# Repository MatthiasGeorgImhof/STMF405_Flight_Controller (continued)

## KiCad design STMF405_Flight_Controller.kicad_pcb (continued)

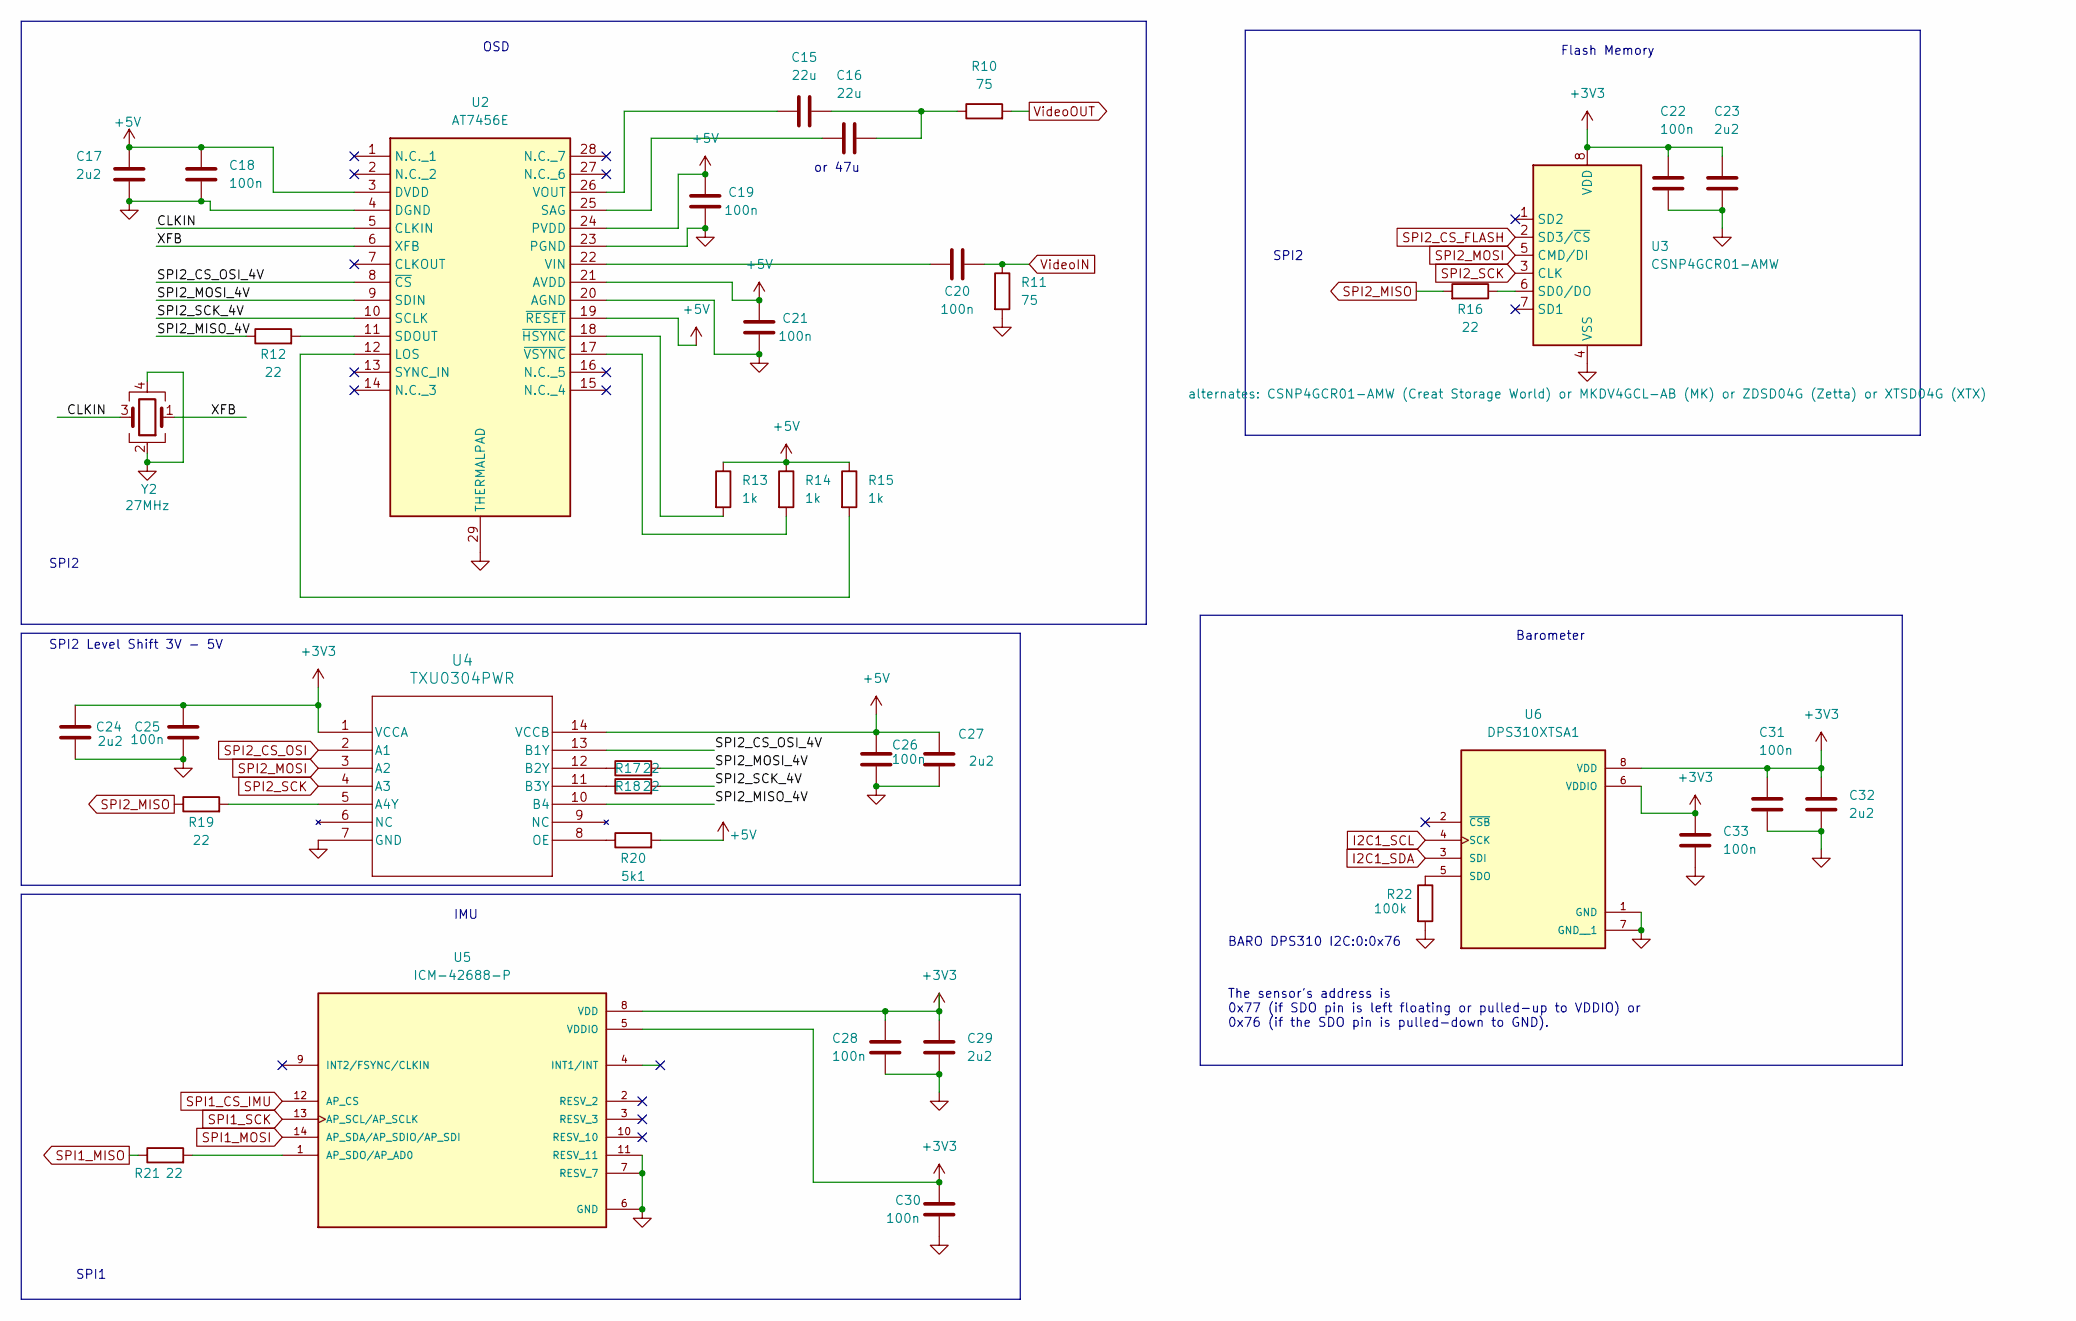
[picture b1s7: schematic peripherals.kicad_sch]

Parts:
C15, C16: 22u; C_0805_2012Metric; Voltage 25; Tolerance 20%; Part Number GRM21BR61E226ME44K
C17, C23, C24, C27, C29, C32: 2u2; C_0402_1005Metric; Voltage 25; Tolerance 10%; Part Number GRT155R61E225KE13D
C18, C19, C20, C21, C22, C25, C26, C28, C30, C31, C33: 100n; C_0201_0603Metric; Voltage 25; Tolerance 10%; Part Number GRM033R61E104KE14J
R10, R11: 75; R_0201_0603Metric; Tolerance 1%; Part Number RC0201FR-0775RL
R12, R16, R17, R18, R19, R21: 22; R_0201_0603Metric; Tolerance 1%; Part Number RC0201FR-0722RL
R13, R14, R15: 1k; R_0201_0603Metric; Tolerance 1%; Part Number RC0201FR-071KL
R20: 5k1; R_0201_0603Metric; Tolerance 1%; Part Number RC0201FR-075K1L
R22: 100k; R_0201_0603Metric; Tolerance 1%; Part Number RC0201FR-07100KL
U2: AT7456E; SOP65P640X120-29N; Part Number AT7456E
U3: CSNP4GCR01-AMW; LGA-8_8x6mm_P1.27mm; Part Number CSNP4GCR01-AMW
U4: TXU0304PWR; TSSOP14_PW_TEX; Part Number TXU0304PWR
U5: ICM-42688-P; LGA-14_3x2.5mm_P0.5mm_LayoutBorder3x4y_no_mask_bridges; Part Number ICM-42688-P
U6: DPS310XTSA1; XDCR_DPS310XTSA1; Part Number DPS310XTSA1
Y2: 27MHz; XTAL_ECS-270-20-30B-TR; Part Number ECS-270-18-30B-JEM-TR

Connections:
+3V3: C22.1, C23.1, C24.1, C25.2, C28.1, C29.1, C30.1, C31.1, C32.1, C33.1, U3.8 (VDD), U4.1 (VCCA), U5.5 (VDDIO), U5.8 (VDD), U6.6 (VDDIO), U6.8 (VDD); also elsewhere on the board
+5V: C17.1, C18.1, C19.2, C21.2, C26.2, C27.1, R13.1, R14.1, R15.1, R20.2, U2.3 (DVDD), U2.19 (~RESET), U2.21 (AVDD), U2.24 (PVDD), U4.14 (VCCB); also elsewhere on the board
/Peripherals/CLKIN: U2.5 (CLKIN), Y2.3
/Peripherals/SPI2_CS_OSI_4V: U2.8 (~CS), U4.13 (B1Y)
/Peripherals/SPI2_MISO_4V: R12.1, U4.10 (B4)
/Peripherals/SPI2_MOSI_4V: R17.2, U2.9 (SDIN)
/Peripherals/SPI2_SCK_4V: R18.2, U2.10 (SCLK)
/Peripherals/XFB: U2.6 (XFB), Y2.1
GND: C17.2, C18.2, C19.1, C21.1, C22.2, C23.2, C24.2, C25.1, C26.1, C27.2, C28.2, C29.2, C30.2, C31.2, C32.2, C33.2, R11.2, R22.2, U2.4 (DGND), U2.20 (AGND), U2.23 (PGND), U2.29 (THERMALPAD), U3.4 (VSS), U4.7 (GND), U5.6 (GND), U5.7 (RESV_7), U5.11 (RESV_11), U6.1 (GND), U6.7 (GND__1), Y2.2, Y2.4; also elsewhere on the board
I2C1_SCL: U6.4 (SCK); also elsewhere on the board
I2C1_SDA: U6.3 (SDI); also elsewhere on the board
unnamed: C15.2, C16.2, R10.1
unnamed: R15.2, U2.12 (LOS)
unnamed: C16.1, U2.25 (SAG)
unnamed: R12.2, U2.11 (SDOUT)
unnamed: C20.1, U2.22 (VIN)
unnamed: C15.1, U2.26 (VOUT)
unnamed: R13.2, U2.18 (~HSYNC)
unnamed: R14.2, U2.17 (~VSYNC)
unnamed: R16.1, U3.6 (SD0/DO)
unnamed: R19.2, U4.5 (A4Y)
unnamed: R17.1, U4.12 (B2Y)
unnamed: R18.1, U4.11 (B3Y)
unnamed: R20.1, U4.8 (OE)
unnamed: R21.2, U5.1 (AP_SDO/AP_AD0)
unnamed: R22.1, U6.5 (SDO)
SPI1_CS_IMU: U5.12 (AP_CS); also elsewhere on the board
SPI1_MISO: R21.1; also elsewhere on the board
SPI1_MOSI: U5.14 (AP_SDA/AP_SDIO/AP_SDI); also elsewhere on the board
SPI1_SCK: U5.13 (AP_SCL/AP_SCLK); also elsewhere on the board
SPI2_CS_FLASH: U3.2 (SD3/~CS); also elsewhere on the board
SPI2_CS_OSI: U4.2 (A1); also elsewhere on the board
SPI2_MISO: R16.2, R19.1; also elsewhere on the board
SPI2_MOSI: U3.5 (CMD/DI), U4.3 (A2); also elsewhere on the board
SPI2_SCK: U3.3 (CLK), U4.4 (A3); also elsewhere on the board
VideoIN: C20.2, R11.1; also elsewhere on the board
VideoOUT: R10.2; also elsewhere on the board

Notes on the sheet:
Barometer
or 47u
OSD
The sensor's address is 0x77 (if SDO pin is left floating or pulled-up to VDDIO) or 0x76 (if the SDO pin is pulled-down to GND).
SPI2
IMU
SPI2 Level Shift 3V - 5V
Flash Memory
SPI1
BARO DPS310 I2C:0:0x76

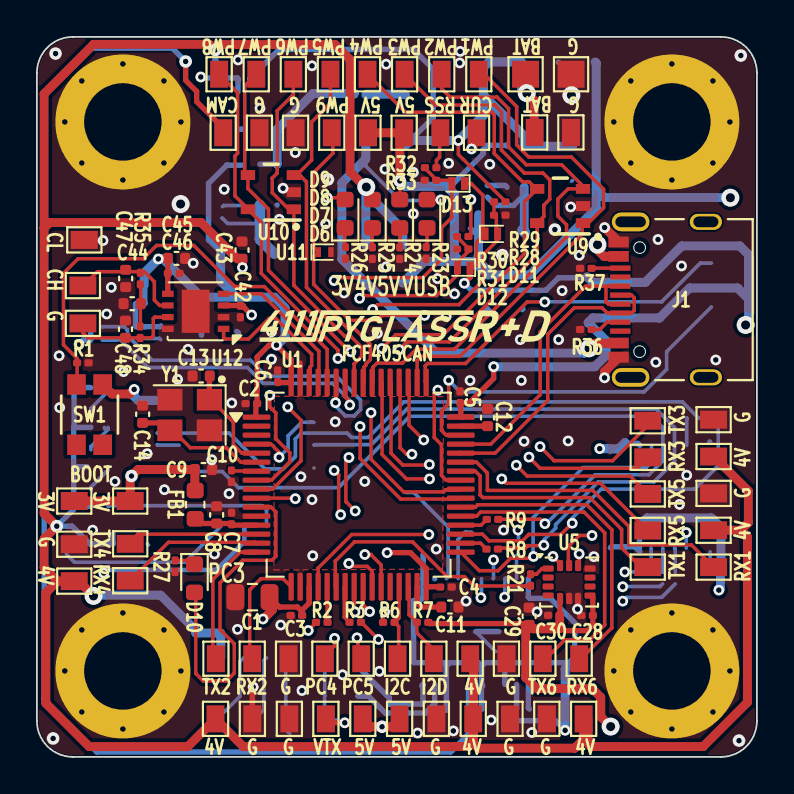
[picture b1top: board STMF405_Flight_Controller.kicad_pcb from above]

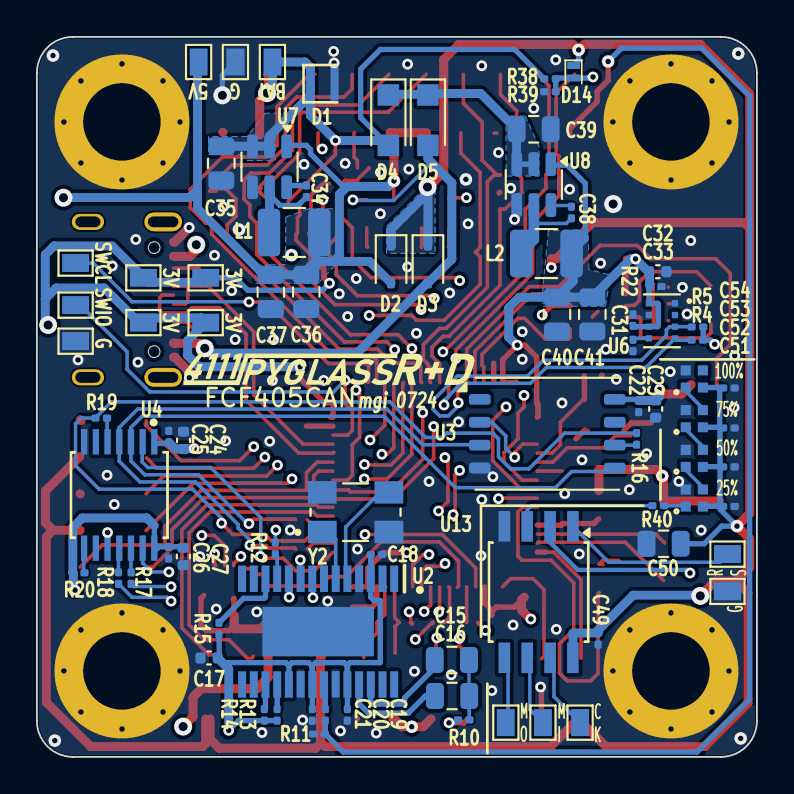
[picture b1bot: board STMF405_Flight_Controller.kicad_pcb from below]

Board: 4 copper layers, 40.0 x 40.0 mm, 212 parts (82 on the bottom side), 113 nets.

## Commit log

2024-07-21 push unclean version
2024-07-21 cleanup pass: step files into step directory
2024-07-21 move step files to step folder
2024-07-21 remove extraneous sym file DPS310XTSA1.kicad_sym
2024-07-24 replace flash memory with SD flash memory; move SPI2 terminations closer to source
2024-07-26 relabel components by sheet and block
2024-07-26 add more gerber files to .gitignore
2024-07-31 remove blind vias and use 0201 resistors
2024-07-31 double check BOM
2024-08-06 remove soldermask bridges for IMU to faciliate assembly by PCBWAY
